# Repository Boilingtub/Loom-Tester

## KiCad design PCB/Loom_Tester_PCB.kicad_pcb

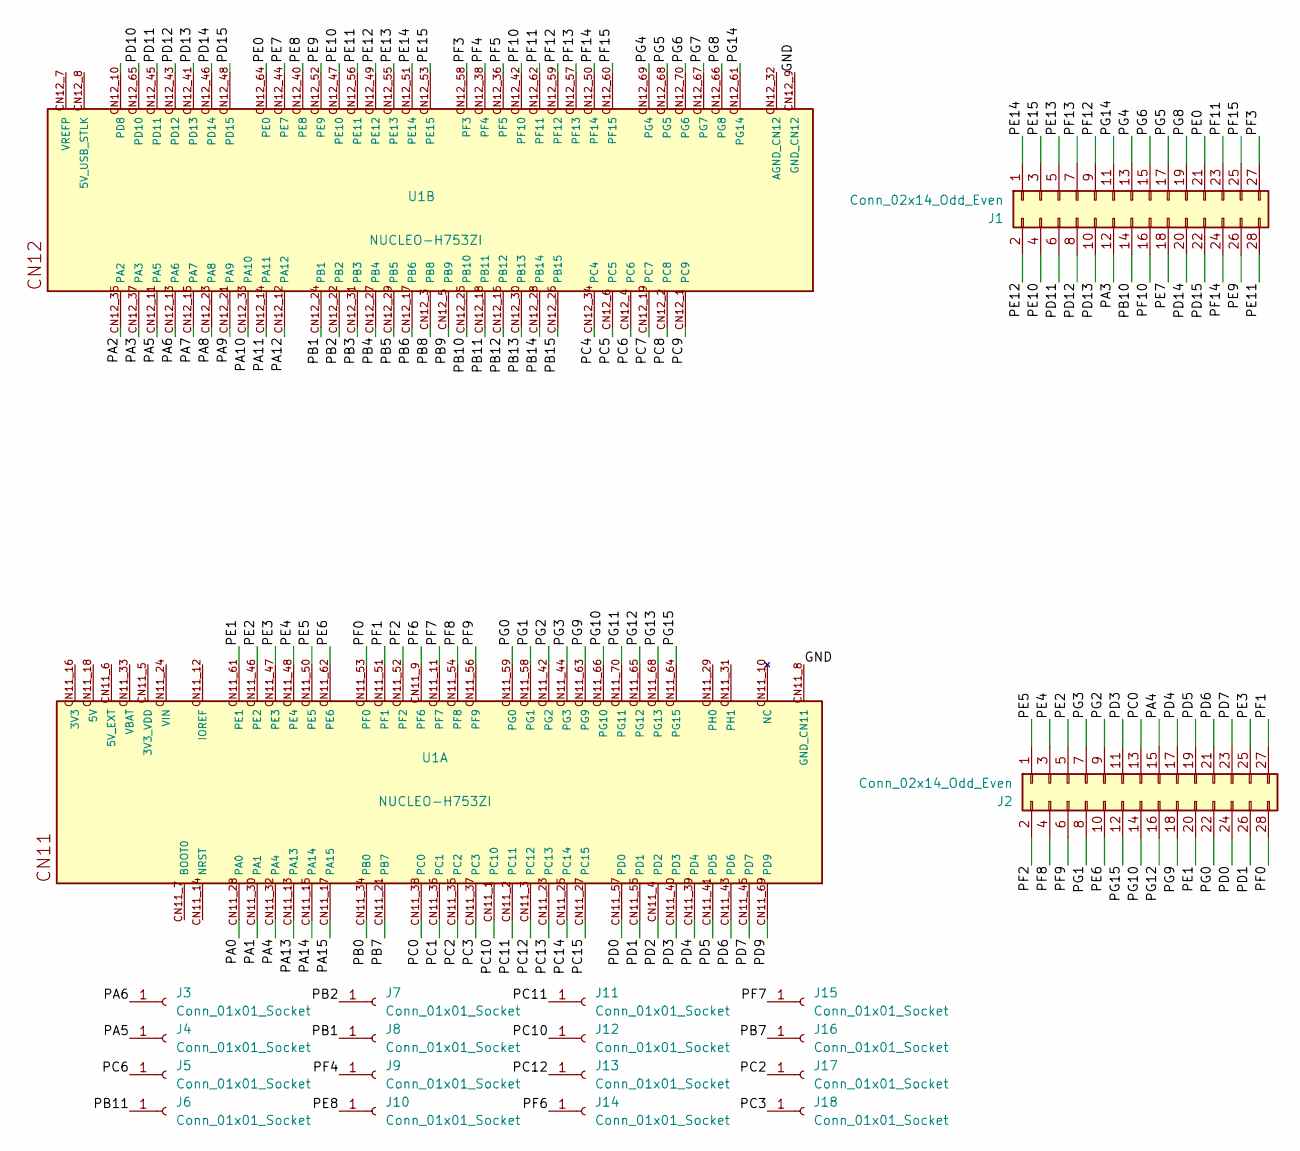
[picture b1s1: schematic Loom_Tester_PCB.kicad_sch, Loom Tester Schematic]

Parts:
J1, J2: Conn_02x14_Odd_Even; PinSocket_2x14_p3.0mm_Vertical
J3, J4, J5, J6, J7, J8, J9, J10, J11, J12, J13, J14, J15, J16, J17, J18: Conn_01x01_Socket; MountingHole_4.3mm_M4_DIN965_Pad
U1: NUCLEO-H753ZI; MODULE_NUCLEO-H753ZI_SMD_INNER; PARTREV Rev. 2

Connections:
/PA0: U1.CN11_28 (PA0)
/PA1: U1.CN11_30 (PA1)
/PA2: U1.CN12_35 (PA2)
/PA3: J1.12, U1.CN12_37 (PA3)
/PA4: J2.15, U1.CN11_32 (PA4)
/PA5: J4.1 (Pin_1_1), U1.CN12_11 (PA5)
/PA6: J3.1 (Pin_1_1), U1.CN12_13 (PA6)
/PA7: U1.CN12_15 (PA7)
/PA8: U1.CN12_23 (PA8)
/PA9: U1.CN12_21 (PA9)
/PA10: U1.CN12_33 (PA10)
/PA11: U1.CN12_14 (PA11)
/PA12: U1.CN12_12 (PA12)
/PA13: U1.CN11_13 (PA13)
/PA14: U1.CN11_15 (PA14)
/PA15: U1.CN11_17 (PA15)
/PB0: U1.CN11_34 (PB0)
/PB1: J8.1 (Pin_1_1), U1.CN12_24 (PB1)
/PB2: J7.1 (Pin_1_1), U1.CN12_22 (PB2)
/PB3: U1.CN12_31 (PB3)
/PB4: U1.CN12_27 (PB4)
/PB5: U1.CN12_29 (PB5)
/PB6: U1.CN12_17 (PB6)
/PB7: J16.1 (Pin_1_1), U1.CN11_21 (PB7)
/PB8: U1.CN12_3 (PB8)
/PB9: U1.CN12_5 (PB9)
/PB10: J1.14, U1.CN12_25 (PB10)
/PB11: J6.1 (Pin_1_1), U1.CN12_18 (PB11)
/PB12: U1.CN12_16 (PB12)
/PB13: U1.CN12_30 (PB13)
/PB14: U1.CN12_28 (PB14)
/PB15: U1.CN12_26 (PB15)
/PC0: J2.13, U1.CN11_38 (PC0)
/PC1: U1.CN11_36 (PC1)
/PC2: J17.1 (Pin_1_1), U1.CN11_35 (PC2)
/PC3: J18.1 (Pin_1_1), U1.CN11_37 (PC3)
/PC4: U1.CN12_34 (PC4)
/PC5: U1.CN12_6 (PC5)
/PC6: J5.1 (Pin_1_1), U1.CN12_4 (PC6)
/PC7: U1.CN12_19 (PC7)
/PC8: U1.CN12_2 (PC8)
/PC9: U1.CN12_1 (PC9)
/PC10: J12.1 (Pin_1_1), U1.CN11_1 (PC10)
/PC11: J11.1 (Pin_1_1), U1.CN11_2 (PC11)
/PC12: J13.1 (Pin_1_1), U1.CN11_3 (PC12)
/PC13: U1.CN11_23 (PC13)
/PC14: U1.CN11_25 (PC14)
/PC15: U1.CN11_27 (PC15)
/PD0: J2.24, U1.CN11_57 (PD0)
/PD1: J2.26, U1.CN11_55 (PD1)
/PD2: U1.CN11_4 (PD2)
/PD3: J2.11, U1.CN11_40 (PD3)
/PD4: J2.17, U1.CN11_39 (PD4)
/PD5: J2.19, U1.CN11_41 (PD5)
/PD6: J2.21, U1.CN11_43 (PD6)
/PD7: J2.23, U1.CN11_45 (PD7)
/PD9: U1.CN11_69 (PD9)
/PD10: U1.CN12_65 (PD10)
/PD11: J1.6, U1.CN12_45 (PD11)
/PD12: J1.8, U1.CN12_43 (PD12)
/PD13: J1.10, U1.CN12_41 (PD13)
/PD14: J1.20, U1.CN12_46 (PD14)
/PD15: J1.22, U1.CN12_48 (PD15)
/PE0: J1.21, U1.CN12_64 (PE0)
/PE1: J2.20, U1.CN11_61 (PE1)
/PE2: J2.5, U1.CN11_46 (PE2)
/PE3: J2.25, U1.CN11_47 (PE3)
/PE4: J2.3, U1.CN11_48 (PE4)
/PE5: J2.1, U1.CN11_50 (PE5)
/PE6: J2.10, U1.CN11_62 (PE6)
/PE7: J1.18, U1.CN12_44 (PE7)
/PE8: J10.1 (Pin_1_1), U1.CN12_40 (PE8)
/PE9: J1.26, U1.CN12_52 (PE9)
/PE10: J1.4, U1.CN12_47 (PE10)
/PE11: J1.28, U1.CN12_56 (PE11)
/PE12: J1.2, U1.CN12_49 (PE12)
/PE13: J1.5, U1.CN12_55 (PE13)
/PE14: J1.1, U1.CN12_51 (PE14)
/PE15: J1.3, U1.CN12_53 (PE15)
/PF0: J2.28, U1.CN11_53 (PF0)
/PF1: J2.27, U1.CN11_51 (PF1)
/PF2: J2.2, U1.CN11_52 (PF2)
/PF3: J1.27, U1.CN12_58 (PF3)
/PF4: J9.1 (Pin_1_1), U1.CN12_38 (PF4)
/PF5: U1.CN12_36 (PF5)
/PF6: J14.1 (Pin_1_1), U1.CN11_9 (PF6)
/PF7: J15.1 (Pin_1_1), U1.CN11_11 (PF7)
/PF8: J2.4, U1.CN11_54 (PF8)
/PF9: J2.6, U1.CN11_56 (PF9)
/PF10: J1.16, U1.CN12_42 (PF10)
/PF11: J1.23, U1.CN12_62 (PF11)
/PF12: J1.9, U1.CN12_59 (PF12)
/PF13: J1.7, U1.CN12_57 (PF13)
/PF14: J1.24, U1.CN12_50 (PF14)
/PF15: J1.25, U1.CN12_60 (PF15)
/PG0: J2.22, U1.CN11_59 (PG0)
/PG1: J2.8, U1.CN11_58 (PG1)
/PG2: J2.9, U1.CN11_42 (PG2)
/PG3: J2.7, U1.CN11_44 (PG3)
/PG4: J1.13, U1.CN12_69 (PG4)
/PG5: J1.17, U1.CN12_68 (PG5)
/PG6: J1.15, U1.CN12_70 (PG6)
/PG7: U1.CN12_67 (PG7)
/PG8: J1.19, U1.CN12_66 (PG8)
/PG9: J2.18, U1.CN11_63 (PG9)
/PG10: J2.14, U1.CN11_66 (PG10)
/PG11: U1.CN11_70 (PG11)
/PG12: J2.16, U1.CN11_65 (PG12)
/PG13: U1.CN11_68 (PG13)
/PG14: J1.11, U1.CN12_61 (PG14)
/PG15: J2.12, U1.CN11_64 (PG15)
GND_CN11: U1.CN11_8 (GND_CN11), U1.CN11_19 (GND_CN11), U1.CN11_20 (GND_CN11), U1.CN11_22 (GND_CN11), U1.CN11_49 (GND_CN11), U1.CN11_60 (GND_CN11), U1.CN11_71 (GND_CN11), U1.CN11_72 (GND_CN11), U1.CN12_9 (GND_CN12), U1.CN12_20 (GND_CN12), U1.CN12_39 (GND_CN12), U1.CN12_54 (GND_CN12), U1.CN12_63 (GND_CN12), U1.CN12_71 (GND_CN12), U1.CN12_72 (GND_CN12)

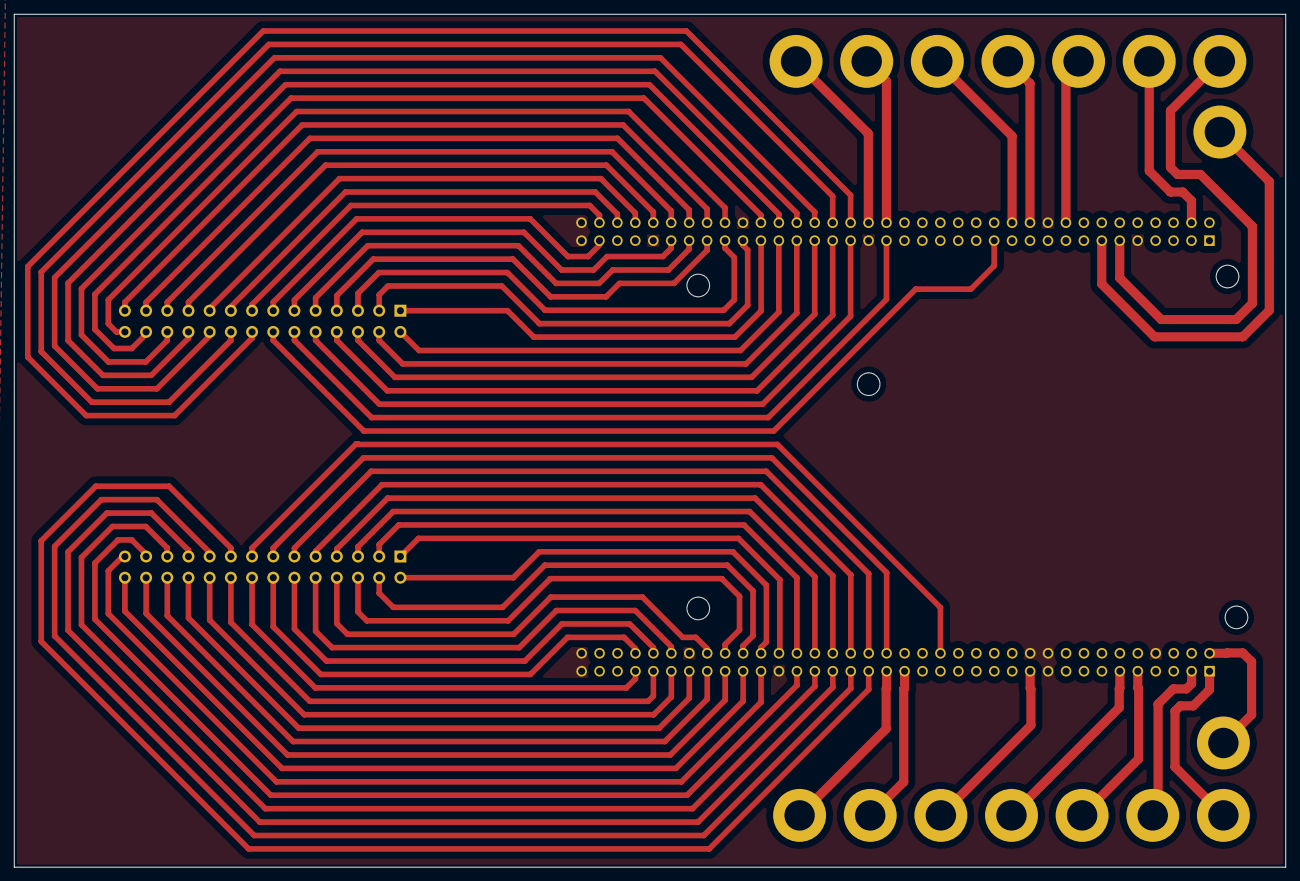
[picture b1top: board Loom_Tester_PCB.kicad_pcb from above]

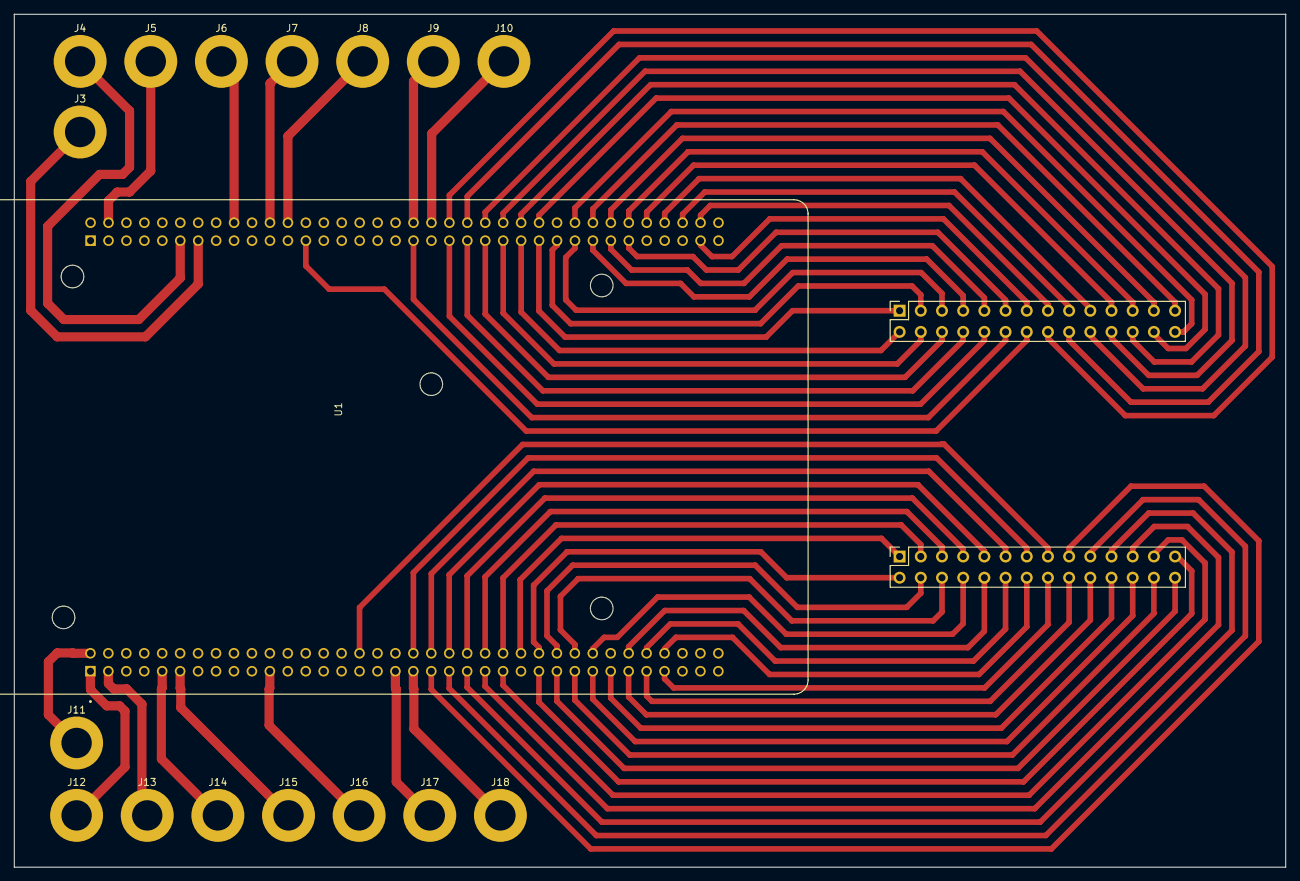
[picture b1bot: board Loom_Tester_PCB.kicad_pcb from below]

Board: 2 copper layers, 180.0 x 120.8 mm, 19 parts (19 on the bottom side), 73 nets.

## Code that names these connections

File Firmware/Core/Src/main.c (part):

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  __HAL_RCC_GPIOG_CLK_ENABLE();
  __HAL_RCC_GPIOD_CLK_ENABLE();

  /*Configure GPIO pins : PE2 PE3 PE4 PE5
                           PE6 PE7 PE9 PE10
                           PE11 PE12 PE13 PE14
                           PE15 PE0 PE1 */
  GPIO_InitStruct.Pin = GPIO_PIN_2|GPIO_PIN_3|GPIO_PIN_4|GPIO_PIN_5
                          |GPIO_PIN_6|GPIO_PIN_7|GPIO_PIN_9|GPIO_PIN_10
                          |GPIO_PIN_11|GPIO_PIN_12|GPIO_PIN_13|GPIO_PIN_14
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  GPIO_InitStruct.Pull = GPIO_PULLDOWN;
  HAL_GPIO_Init(GPIOE, &GPIO_InitStruct);

  /*Configure GPIO pins : PF0 PF1 PF2 PF3
                           PF8 PF9 PF10 PF11
                           PF12 PF13 PF14 PF15 */
  GPIO_InitStruct.Pin = GPIO_PIN_0|GPIO_PIN_1|GPIO_PIN_2|GPIO_PIN_3
                          |GPIO_PIN_8|GPIO_PIN_9|GPIO_PIN_10|GPIO_PIN_11
                          |GPIO_PIN_12|GPIO_PIN_13|GPIO_PIN_14|GPIO_PIN_15;
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  GPIO_InitStruct.Pull = GPIO_PULLDOWN;
  HAL_GPIO_Init(GPIOF, &GPIO_InitStruct);

  /*Configure GPIO pins : PF4 PF6 PF7 */
  GPIO_InitStruct.Pin = GPIO_PIN_4|GPIO_PIN_6|GPIO_PIN_7;
  GPIO_InitStruct.Mode = GPIO_MODE_INPUT;
  GPIO_InitStruct.Pull = GPIO_NOPULL;
  HAL_GPIO_Init(GPIOF, &GPIO_InitStruct);

  /*Configure GPIO pin : PC0 */
  GPIO_InitStruct.Pin = GPIO_PIN_0;
  GPIO_InitStruct.Mode = GPIO_MODE_INPUT;
  GPIO_InitStruct.Pull = GPIO_PULLDOWN;
  HAL_GPIO_Init(GPIOC, &GPIO_InitStruct);

  /*Configure GPIO pins : PC2 PC3 PC6 PC8
                           PC9 PC10 PC11 PC12 */
  GPIO_InitStruct.Pin = GPIO_PIN_2|GPIO_PIN_3|GPIO_PIN_6|GPIO_PIN_8
                          |GPIO_PIN_9|GPIO_PIN_10|GPIO_PIN_11|GPIO_PIN_12;
  GPIO_InitStruct.Mode = GPIO_MODE_INPUT;
  GPIO_InitStruct.Pull = GPIO_NOPULL;
  HAL_GPIO_Init(GPIOC, &GPIO_InitStruct);

  /*Configure GPIO pins : PA3 PA4 */
  GPIO_InitStruct.Pin = GPIO_PIN_3|GPIO_PIN_4;
  GPIO_InitStruct.Mode = GPIO_MODE_INPUT;
  GPIO_InitStruct.Pull = GPIO_PULLDOWN;
  HAL_GPIO_Init(GPIOA, &GPIO_InitStruct);

  /*Configure GPIO pins : PA5 PA6 */
  GPIO_InitStruct.Pin = GPIO_PIN_5|GPIO_PIN_6;
  GPIO_InitStruct.Mode = GPIO_MODE_INPUT;
  GPIO_InitStruct.Pull = GPIO_NOPULL;
  HAL_GPIO_Init(GPIOA, &GPIO_InitStruct);

  /*Configure GPIO pins : PB1 PB2 PB11 PB7 */
  GPIO_InitStruct.Pin = GPIO_PIN_1|GPIO_PIN_2|GPIO_PIN_11|GPIO_PIN_7;
  GPIO_InitStruct.Mode = GPIO_MODE_INPUT;
  GPIO_InitStruct.Pull = GPIO_NOPULL;
  HAL_GPIO_Init(GPIOB, &GPIO_InitStruct);

  /*Configure GPIO pins : PG0 PG1 PG2 PG3
                           PG4 PG5 PG6 PG8
                           PG9 PG10 PG12 PG14
                           PG15 */
  GPIO_InitStruct.Pin = GPIO_PIN_0|GPIO_PIN_1|GPIO_PIN_2|GPIO_PIN_3
                          |GPIO_PIN_4|GPIO_PIN_5|GPIO_PIN_6|GPIO_PIN_8
                          |GPIO_PIN_9|GPIO_PIN_10|GPIO_PIN_12|GPIO_PIN_14
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  GPIO_InitStruct.Pull = GPIO_PULLDOWN;
  HAL_GPIO_Init(GPIOG, &GPIO_InitStruct);

  /*Configure GPIO pin : PE8 */
  GPIO_InitStruct.Pin = GPIO_PIN_8;
  GPIO_InitStruct.Mode = GPIO_MODE_INPUT;
  GPIO_InitStruct.Pull = GPIO_NOPULL;
  HAL_GPIO_Init(GPIOE, &GPIO_InitStruct);

  /*Configure GPIO pins : PD11 PD12 PD13 PD14
                           PD15 PD0 PD1 PD3
                           PD4 PD5 PD6 PD7 */
  GPIO_InitStruct.Pin = GPIO_PIN_11|GPIO_PIN_12|GPIO_PIN_13|GPIO_PIN_14
                          |GPIO_PIN_15|GPIO_PIN_0|GPIO_PIN_1|GPIO_PIN_3
                          |GPIO_PIN_4|GPIO_PIN_5|GPIO_PIN_6|GPIO_PIN_7;
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

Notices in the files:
Firmware/Core/Src/main.c:
Copyright (c) 2026 STMicroelectronics.
All rights reserved.
This software is licensed under terms that can be found in the LICENSE file
